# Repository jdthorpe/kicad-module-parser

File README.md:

# Convert Kicad Board and Module files to JSON

Do you love working with S-Expressions? Me either. Convert your Kicad board
and module files to JSON or YAML and use your favorite tools to work with
your Kicad board and module file data!

## CLI Usage

When installed globally (`npm i -g kicad-to-json`), npm installs the
`k2j` command line tool, which converts your kicad files to json like so:

```sh
k2j ./my_module_file.kicad_mod
# creates ./my_module_file.json in compact format

k2j ./my_board_file.kicad_pcb --yaml --format long
# creates ./my_board_file.yaml in long format
```

Use the `-h` flag for the usual help:

```txt
usage: index.js [-h] [-o OUTPUT] [-f {compact,long,bare}] [-v] [--yaml] file

Convert Kicad board and module files to JSON/YAML

positional arguments:
  file                  The Kicad pcb or module file to convert to json

optional arguments:
  -h, --help            show this help message and exit
  -o OUTPUT, --output OUTPUT
                        Output file (defaults to input file with '.json' or '.yaml' extension)
  -f {compact,long,bare}, --format {compact,long,bare}
                        Set the output format
  -v, --verbose         verbose output
  --yaml                set output to yaml
```

## Javascript / Typescript Usage

User friendly data

```ts
import { parse } from "kicad-module-parser"

// convert the module (string) to compact format
const my_module = parse.module(kicad_mod_contents_string)

// convert the board (string) to long format
const my_board = parse.board(kicad_pcb_contents_string,"long")
```

## Output Formats

### Background

The `kicad_mod` and `kicad_pcb` files are S-Expressions based which have
the general format `(name  ...contents )` where the contents are either
individual values or nested s-expressions (e.g. `( pts (xy 1 1) (xy 2 2))`).
Some s-expressions are singletons, such as the `pts` expression within a
`polygon` and others can appear multiple times, such as the individual `xy`
pairs within an array of points.

### `bare` Notation

In the `bare` notation the first token in the s-expresion appears as it's `type`
attribute, and the remaining sub-expression appear in the `value` attribute.
This format is quite literal, but generally hard to work with.  Here is a brief
example (in yaml format):

```yaml
type: kicad_pcb
value:
  - type: version
    value:
      type: number
      value: '20171130'
  - type: general
    value:
      - type: thickness
        value:
          type: number
          value: '1.6'
      - type: drawings
        value:
          type: number
          value: '605'
      - type: tracks
        value:
          type: number
          value: '2555'
      - type: zones
        value:
          type: number
          value: '0'
      - type: modules
        value:
          type: number
          value: '172'
```

### `compact` Notation

In the compact format, s-expression types and values from the bare format are
used as key-value pairs of a JSON object This works for s-expressions that are
singletons, but for expressions like `(add_net GND) (add_net +3v3)` which may
appear multiple times within the parent s-expression, the contents of the
expression are included in an array of the same name, such as :

```json
{
    "add_net":[
        {"net_name": "GND"},
        {"net_name": "+3v3"}
    ]
}
```

Here is the same example from above in compact format:

```yaml
kicad_pcb:
  version: 20171130
  general:
    thickness: 1.6
    drawings: 605
    tracks: 2555
    zones: 0
    modules: 172
    nets: 143
```

### `long` Notation

The `long` format is a hybrid between the Compact and Bare formats, and
recoginses that module and board files are special, in that nearly every file
will have *many* repeating entities (such as `gr_lines`) where preserving the
order of the entites may be useful.  Hence, the immediate children of boards and
modules (and modules nested within boards) are represent in bare format, and
everything else is represented in compact format. Here is the same example from
above in long format:

```yaml
kicad_pcb:
  - type: version
    value: 20171130
  - type: general
    value:
      thickness: 1.6
      drawings: 605
      tracks: 2555
      zones: 0
      modules: 172
      nets: 143
```

## `bare` Format Details

There are 4 primitives in the bare format which have type `"string"`, `"hex"`,
`"number"` and `"boolean"`, such as:

```json
{ "type": "string", "value": "GND" }
{ "type": "hex", "value": "1234ABCD" }
{ "type": "number", "value": "3.2" } // yes, numbers are represented as strings
{ "type": "boolean", "value": true }
```

The array type has a `type` attribute of `"array"` and a `value` contianing an
aray of primitives, such as:

```json
{ "type": "array", "value": [ { "type": "string", "value": "GND" } ] }
```

The `container` type is like the `array` type but it's `type` attribute has a
value other than `"string"`, `"hex"`, `"number"`, `"boolean"` or `"array"`, and
the value can contain any type (including other containers), or an array
containing any of the types, sucy as:

```json
{
  "type": "xy",
  "value": [
    {
      "type": "x",
      "value": {
        "type": "number",
        "value": "117.4"
      }
    },
    {
      "type": "y",
      "value": {
        "type": "number",
        "value": "28"
      }
    }
  ]
}
```

## Final notes

There are a handfule of sub-parsers and things I was not personally
interested in (such as page formatting) which result in a value like
`"page info": "unsupported"`. If you despirately need page info (or any other
unsupported features), I welcome your pull request!

If your board or module results in an error, please put it in a github repo (or
a minimal example that raises the same error), and open an issue with a link to
that github repo.

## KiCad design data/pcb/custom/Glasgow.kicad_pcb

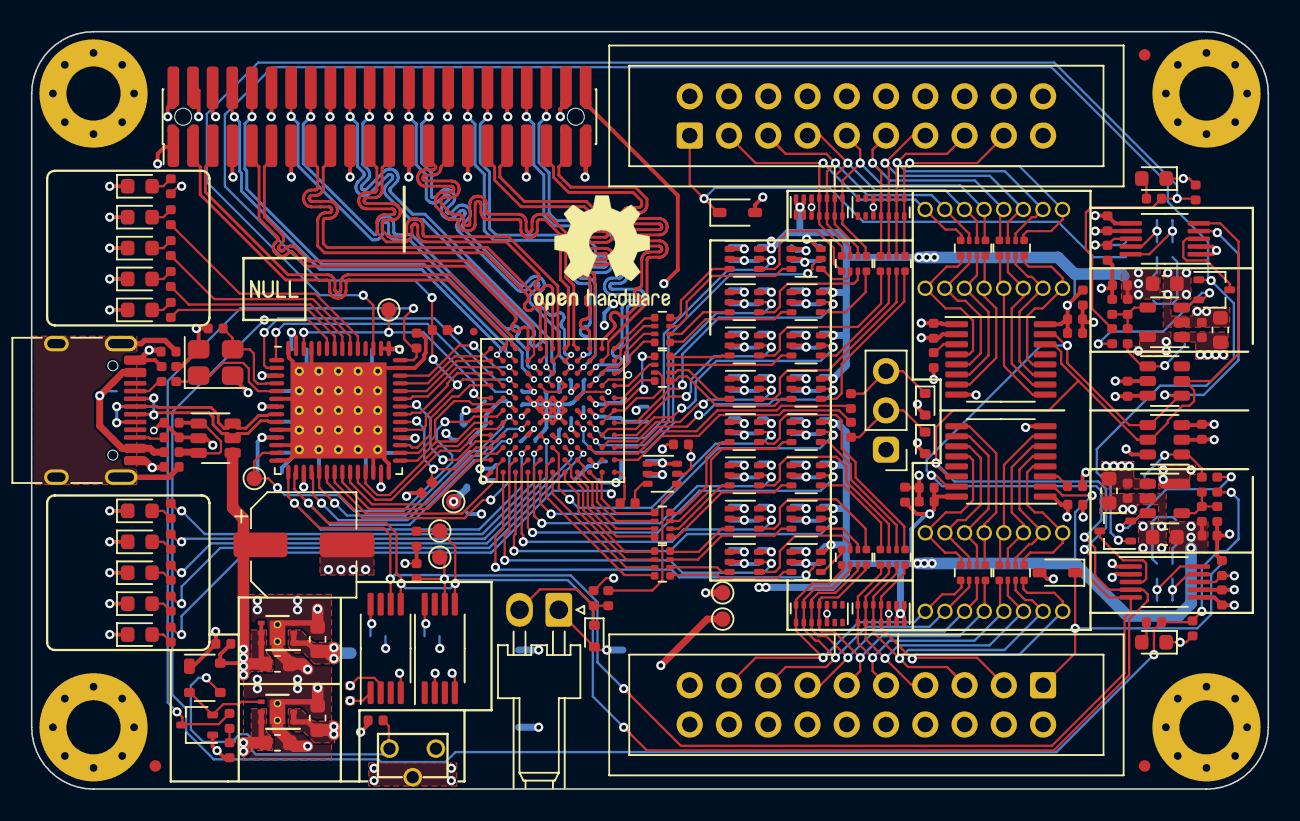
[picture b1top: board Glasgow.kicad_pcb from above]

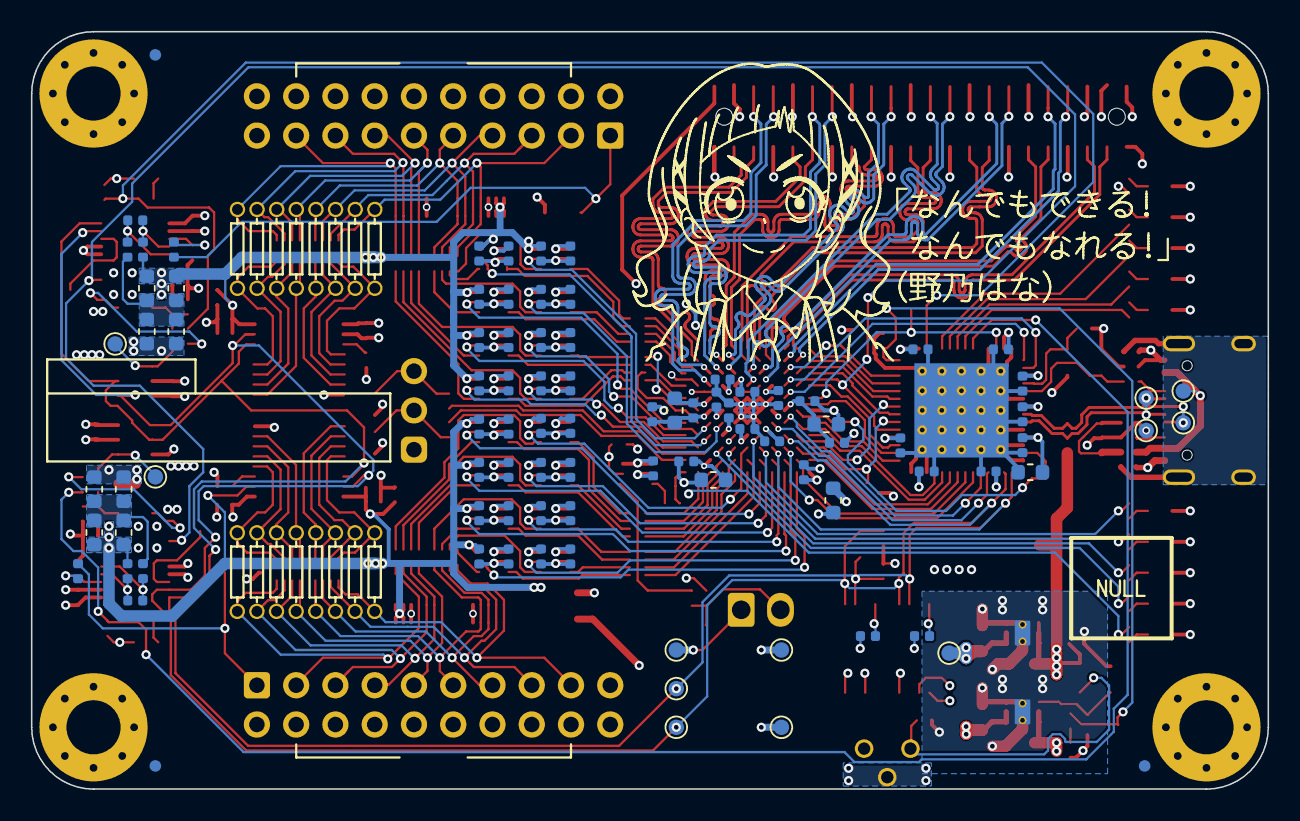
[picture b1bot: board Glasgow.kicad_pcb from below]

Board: 4 copper layers, 80.0 x 49.0 mm, 264 parts (93 on the bottom side), 226 nets.

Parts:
C1, C14, C19, C26, C27, C28, C31, C53, C76, C80, C82, C83, C86: 4u7; C_0603_1608Metric
C2, C3, C4, C5, C6, C7, C8, C9, C10, C13, C15, C16, C17, C18, C20, C21, C22, C23, C24, C25, C29, C30, C32, C33, C34, C35, C36, C37, C38, C39, C40, C41, C42, C43, C44, C45, C46, C47, C48, C49, C50, C51, C52, C54, C55, C56, C57, C58, C59, C60, C61, C62, C63, C64, C65, C66, C67, C68, C69, C70, C71, C72, C73, C74, C75, C77, C78, C79, C81, C84, C85, C88, C89: u1; C_0402_1005Metric
C11, C12: 9p; C_0402_1005Metric
C87: 150u; CP_Elec_6.3x5.9
C90, C91: DNP; C_0402_1005Metric_DNP
D1, D2, D3, D14, D15: GRN; LED_0603_1608Metric
D4: YEL; LED_0603_1608Metric
D5: RED; LED_0603_1608Metric
D6, D10: BLU; LED_0603_1608Metric
D7, D9: PNK; LED_0603_1608Metric
D8: WHT; LED_0603_1608Metric
D11, D12, D13: ESD5Z5.0T1G; D_SOD-523
D16, D17: CDSOD323-T36S; D_SOD-323
D18, D19: BAT54CW; SOT-323_SC-70
D20, D21, D22, D23: SP3012-06UTG; UDFN-14_3.5x1.35mm_P0.5mm
D24: BAT54AW; SOT-323_SC-70
FB1: 600R, 0.5A; L_0402_1005Metric
FID1, FID2, FID3, FID4, FID5, FID6: Fiducial_0.75mm_Mask1.5mm
FID8: Fiducial_0.5mm_Dia_1mm_Outer
J1: USB_C_USB2.0; USB_C_Receptacle_HRO_TYPE-C-31-M-12
J2, J3: IDC-Header_2x10_P2.54mm; IDC-Header_2x10_P2.54mm_Vertical
J4: Conn_01x02; Molex_KK-254_1x02_P2.54mm_Horizontal
J5: PinHeader_2x22_P1.27mm; PinHeader_2x22_P1.27mm_Vertical__SMD
J6, J7, J8, J9: Conn_01x08; PinSocket_1x08_P1.27mm_Vertical_DNP
J10: AUX; PinHeader_1x03_P2.54mm_Vertical
MK1, MK2, MK3, MK4: Mounting_Hole_PAD; MountingHole_3.5mm_Pad_Via_CrtYd
NONO_HANA: MECHOKKU; nono_hana_lines
R1, R2, R10, R15, R41, R42, R57, R58: 2k2; R_0402_1005Metric
R3, R4, R5, R9, R17: 100k; R_0402_1005Metric
R6, R8, R50, R51: DNP; R_0603_1608Metric_DNP
R7, R56: 0R33; R_0603_1608Metric
R11, R23: 4k7; R_0402_1005Metric
R12, R13, R14, R46, R47: 20k; R_0402_1005Metric
R16, R18, R19, R20, R22, R26, R36, R37, R44, R55: 10k; R_0402_1005Metric
R21: 6k8; R_0402_1005Metric
R24, R25, R30, R54, R59, R60: 4R7; R_0402_1005Metric
R27, R33: 49k9; R_0402_1005Metric
R28, R34: 59k; R_0402_1005Metric
R29, R35: 24k3; R_0402_1005Metric
R31, R32: 100R; R_0402_1005Metric
R38, R39, R43, R45: 47R; R_0402_1005Metric
R40: DNP; R_0402_1005Metric_DNP
R48, R49: 0R15; R_0603_1608Metric
R52, R53: 5k1; R_0402_1005Metric
RN1, RN2, RN3, RN4, RN7, RN8, RN9, RN10: 33R; R_Array_Convex_4x0402
RN5, RN6, RN11, RN12: 10k; R_Array_Convex_4x0402
SW1: RST; SW_Tactile_SPST_Angled_TC-1109DE
TP1, TP8: 5V; TestPoint_Pad_D1.0mm
TP2, TP17: 1V2; TestPoint_Pad_D1.0mm
TP3, TP7, TP9: 3V3; TestPoint_Pad_D1.0mm
TP4, TP10: SDA; TestPoint_Pad_D1.0mm
TP5, TP11: SCL; TestPoint_Pad_D1.0mm
TP6: CLKREF; TestPoint_Pad_D1.0mm
TP12: GND; TestPoint_Pad_D1.0mm
TP13: VBUS; TestPoint_Pad_D1.0mm
TP14: USBGND; TestPoint_Pad_D1.0mm
TP15: USBDP; TestPoint_Pad_D1.0mm
TP16: USBDM; TestPoint_Pad_D1.0mm
TP18, TP19: VDAC; TestPoint_Pad_D1.0mm
U1: CY7C68013A-56LTX; Cypress_QFN-56-1EP_8x8mm_P0.5mm_EP6.22x6.22mm_ThermalVias
U2: CAT24M01X; TSSOP-8_4.4x3mm_P0.65mm
U3: BL24C256A-SFRC; TSSOP-8_4.4x3mm_P0.65mm
U4, U6, U9, U10, U11, U16, U17, U18, U22, U23, U24, U25, U26, U27, U28, U29, U32: SN74LVC1T45DCKR; SOT-363_SC-70-6
U5, U19: PCA6408APW; TSSOP-16_4.4x5mm_P0.65mm
U7: APX811-40UG-7; SOT-143
U8: TLV75533PDRVR; DFN-6-1EP_2x2mm_P0.65mm_EP1x1.6mm_ThermalVias
U12, U21: INA233; VSSOP-10_3x3mm_P0.5mm
U13, U20: DAC081C081CIMK; SOT-23-6
U14, U31: TPS73101DBV; SOT-23-5
U15: TPD3S014; SOT-23-6
U30: ICE40HX8K-BG121; BGA-121_9.0x9.0mm_Layout11x11_P0.8mm_Ball0.4mm_Pad0.35mm_NS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
U36: TLV73312PQDRVR; DFN-6-1EP_2x2mm_P0.65mm_EP1x1.6mm_ThermalVias
Y1: 24M; Crystal_SMD_3225-4Pin_3.2x2.5mm

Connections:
+1V2: C14.1, C18.1, C24.1, C25.1, C27.1, C77.1, R31.2, R32.2, TP2.1, TP17.1, U30.D4, U30.D8, U30.H4, U30.H8, U36.1, U36.2
+3V3: C1.1, C2.1, C3.1, C4.1, C5.1, C6.1, C7.1, C9.1, C10.1, C15.1, C17.1, C19.1, C20.1, C21.1, C22.1, C23.1, C28.1, C30.1, C32.1, C34.1, C35.1, C36.1, C37.1, C42.1, C43.1, C47.1, C48.1, C55.1, C56.1, C60.1, C61.1, C62.1, C63.1, C68.1, C69.1, C70.1, C71.1, C81.1, C84.1, C85.1, D24.1, J5.2, R1.2, R2.2, R4.1, R12.1, R17.2, R36.2, R37.2, R40.2, R44.2, TP3.1, TP9.1, U1.3, U1.7, U1.11, U1.17, U1.27, U1.32, U1.43, U1.44, U1.55, U2.2, U2.8, U3.1, U3.8, U4.1, U5.1, U6.1, U8.1, U8.2, U9.1, U10.1, U11.1, U12.2, U12.6, U13.2, U16.1, U17.1, U18.1, U19.1, U20.2, U21.6, U22.1, U23.1, U24.1, U25.1, U26.1, U27.1, U28.1, U29.1, U30.C10, U30.D6, U30.F8, U30.H6, U30.L11, U32.1, U32.6
+5V: C16.1, C26.2, C31.1, C45.1, C59.1, C82.1, C86.2, C87.1, TP1.1, TP8.1, U7.4, U8.5, U8.6, U14.1, U15.4, U31.1, U36.4, U36.5, U36.6
/A0: U1.37, U30.K3
/A1: U1.38, U30.L2
/CC1: J1.A5, R53.2
/CC2: J1.B5, R52.2
/CLKIF: TP7.1, U1.13, U30.K6
/CLKREF: TP6.1, U1.54, U30.D5, U30.L5
/D0: U1.18, U30.H7
/D1: U1.19, U30.J7
/D2: U1.20, U30.J9
/D3: U1.21, U30.K10
/D4: U1.22, U30.L10
/D5: U1.23, U30.K9
/D6: U1.24, U30.L8
/D7: U1.25, U30.K7
/ENVA: R18.1, R47.1, R55.2, U1.45
/ENVB: R19.1, R26.2, R46.1, U1.51
/FLAGA: U1.29, U30.L7
/FLAGB: U1.30, U30.K5
/FLAGC: U1.31, U30.L4
/FLAGD: U1.40, U30.J3
/FPGA_DONE: U1.36, U30.K8
/GNDPLL0: C76.2, C78.2, U30.L6
/GNDPLL1: C79.2, C80.2, U30.C5
/IO_Banks/DA0: U4.5, U30.C7
/IO_Banks/DA1: U11.5, U30.C8
/IO_Banks/DA2: U6.5, U30.D7
/IO_Banks/DA3: U16.5, U30.A7
/IO_Banks/DA4: U9.5, U30.B8
/IO_Banks/DA5: U17.5, U30.A8
/IO_Banks/DA6: U10.5, U30.B9
/IO_Banks/DA7: U18.5, U30.A9
/IO_Banks/DB0: U22.5, U30.F9
/IO_Banks/DB1: U26.5, U30.G11
/IO_Banks/DB2: U23.5, U30.G10
/IO_Banks/DB3: U27.5, U30.H11
/IO_Banks/DB4: U24.5, U30.H10
/IO_Banks/DB5: U28.5, U30.J11
/IO_Banks/DB6: U25.5, U30.J10
/IO_Banks/DB7: U29.5, U30.K11
/IO_Banks/IO_Buffer_A/ISNS_H: R8.2, R30.1, R49.1, R51.1, R56.2
/IO_Banks/IO_Buffer_A/P0: J9.1, RN11.5, U19.4
/IO_Banks/IO_Buffer_A/P1: J9.2, RN11.6, U19.5
/IO_Banks/IO_Buffer_A/P2: J9.3, RN11.7, U19.6
/IO_Banks/IO_Buffer_A/P3: J9.4, RN11.8, U19.7
/IO_Banks/IO_Buffer_A/P4: J9.5, RN12.5, U19.9
/IO_Banks/IO_Buffer_A/P5: J9.6, RN12.6, U19.10
/IO_Banks/IO_Buffer_A/P6: J9.7, RN12.7, U19.11
/IO_Banks/IO_Buffer_A/P7: J9.8, RN12.8, U19.12
/IO_Banks/IO_Buffer_A/VDAC: R33.1, TP19.1, U20.1
/IO_Banks/IO_Buffer_A/VFB: R33.2, R34.1, R35.2, U31.4
/IO_Banks/IO_Buffer_A/VIO_EN: D19.2, R55.1, U31.3
/IO_Banks/IO_Buffer_A/VSENSE: D17.1, J2.1, R60.2
/IO_Banks/IO_Buffer_A/X0: RN7.8, U4.3
/IO_Banks/IO_Buffer_A/Y0: RN9.1, U4.4
/IO_Banks/IO_Buffer_A/Y1: RN9.2, U11.4
/IO_Banks/IO_Buffer_A/Y2: RN9.3, U6.4
/IO_Banks/IO_Buffer_A/Y3: RN9.4, U16.4
/IO_Banks/IO_Buffer_A/Y4: RN10.1, U9.4
/IO_Banks/IO_Buffer_A/Y5: RN10.2, U17.4
/IO_Banks/IO_Buffer_A/Y6: RN10.3, U10.4
/IO_Banks/IO_Buffer_A/Y7: RN10.4, U18.4
/IO_Banks/IO_Buffer_A/Z0: D22.4, D22.11, J2.3, J8.1, RN9.8, RN11.4
/IO_Banks/IO_Buffer_A/Z1: D22.3, D22.12, J2.5, J8.2, RN9.7, RN11.3
/IO_Banks/IO_Buffer_A/Z2: D22.2, D22.13, J2.7, J8.3, RN9.6, RN11.2
/IO_Banks/IO_Buffer_A/Z3: D22.1, D22.14, J2.9, J8.4, RN9.5, RN11.1
/IO_Banks/IO_Buffer_A/Z4: D23.4, D23.11, J2.11, J8.5, RN10.8, RN12.4
/IO_Banks/IO_Buffer_A/Z5: D23.3, D23.12, J2.13, J8.6, RN10.7, RN12.3
/IO_Banks/IO_Buffer_A/Z6: D23.2, D23.13, J2.15, J8.7, RN10.6, RN12.2
/IO_Banks/IO_Buffer_A/Z7: D23.1, D23.14, J2.17, J8.8, RN10.5, RN12.1
/IO_Banks/IO_Buffer_B/ISNS_H: R6.2, R7.2, R24.1, R48.1, R50.1
/IO_Banks/IO_Buffer_B/P0: J7.1, RN5.5, U5.4
/IO_Banks/IO_Buffer_B/P1: J7.2, RN5.6, U5.5
/IO_Banks/IO_Buffer_B/P2: J7.3, RN5.7, U5.6
/IO_Banks/IO_Buffer_B/P3: J7.4, RN5.8, U5.7
/IO_Banks/IO_Buffer_B/P4: J7.5, RN6.5, U5.9
/IO_Banks/IO_Buffer_B/P5: J7.6, RN6.6, U5.10
/IO_Banks/IO_Buffer_B/P6: J7.7, RN6.7, U5.11
/IO_Banks/IO_Buffer_B/P7: J7.8, RN6.8, U5.12
/IO_Banks/IO_Buffer_B/VDAC: R27.1, TP18.1, U13.1
/IO_Banks/IO_Buffer_B/VFB: R27.2, R28.1, R29.2, U14.4
/IO_Banks/IO_Buffer_B/VIO_EN: D18.2, R26.1, U14.3
/IO_Banks/IO_Buffer_B/VSENSE: D16.1, J3.1, R59.2
/IO_Banks/IO_Buffer_B/X0: RN1.8, U22.3
/IO_Banks/IO_Buffer_B/Y0: RN3.1, U22.4
/IO_Banks/IO_Buffer_B/Y1: RN3.2, U26.4
/IO_Banks/IO_Buffer_B/Y2: RN3.3, U23.4
/IO_Banks/IO_Buffer_B/Y3: RN3.4, U27.4
/IO_Banks/IO_Buffer_B/Y4: RN4.1, U24.4
/IO_Banks/IO_Buffer_B/Y5: RN4.2, U28.4
/IO_Banks/IO_Buffer_B/Y6: RN4.3, U25.4
/IO_Banks/IO_Buffer_B/Y7: RN4.4, U29.4
/IO_Banks/IO_Buffer_B/Z0: D20.4, D20.11, J3.3, J6.1, RN3.8, RN5.4
/IO_Banks/IO_Buffer_B/Z1: D20.3, D20.12, J3.5, J6.2, RN3.7, RN5.3
/IO_Banks/IO_Buffer_B/Z2: D20.2, D20.13, J3.7, J6.3, RN3.6, RN5.2
/IO_Banks/IO_Buffer_B/Z3: D20.1, D20.14, J3.9, J6.4, RN3.5, RN5.1
/IO_Banks/IO_Buffer_B/Z4: D21.4, D21.11, J3.11, J6.5, RN4.8, RN6.4
/IO_Banks/IO_Buffer_B/Z5: D21.3, D21.12, J3.13, J6.6, RN4.7, RN6.3
/IO_Banks/IO_Buffer_B/Z6: D21.2, D21.13, J3.15, J6.7, RN4.6, RN6.2
/IO_Banks/IO_Buffer_B/Z7: D21.1, D21.14, J3.17, J6.8, RN4.5, RN6.1
/IO_Banks/QA0: RN7.1, U30.A1
/IO_Banks/QA1: RN7.2, U30.A2
/IO_Banks/QA2: RN7.3, U30.B3
/IO_Banks/QA3: RN7.4, U30.A3
/IO_Banks/QA4: RN8.1, U30.B5, U30.B6
/IO_Banks/QA5: RN8.2, U30.A4
/IO_Banks/QA6: RN8.3, U30.A6, U30.B7
/IO_Banks/QA7: RN8.4, U30.A5
/IO_Banks/QB0: RN1.1, U30.B11
/IO_Banks/QB1: RN1.2, U30.C11
/IO_Banks/QB2: RN1.3, U30.D10
/IO_Banks/QB3: RN1.4, U30.D11
/IO_Banks/QB4: RN2.1, U30.E10
/IO_Banks/QB5: RN2.2, U30.E11
/IO_Banks/QB6: RN2.3, U30.F11
/IO_Banks/QB7: RN2.4, U30.F10
/IO_Banks/U1: R11.1, U30.G9
/IO_Banks/U2: R20.1, U30.G8
/IO_Banks/U3: R21.1, U30.E9
/IO_Banks/U4: R22.1, U30.D9
/IO_Banks/U5: R23.1, U30.E8
/IO_Banks/VIOA: C38.1, C39.1, C40.1, C41.1, C49.1, C50.1, C51.1, C52.1, C54.1, C57.1, C83.1, D22.6, D22.7, D22.8, D22.9, J2.2, R34.2, R42.2, R49.2, R51.2, R54.1, R58.2, U4.6, U6.6, U9.6, U10.6, U11.6, U16.6, U17.6, U18.6, U19.16
/IO_Banks/VIOB: C29.1, C46.1, C53.1, C64.1, C65.1, C66.1, C67.1, C72.1, C73.1, C74.1, C75.1, D20.6, D20.7, D20.8, D20.9, J3.2, R25.1, R28.2, R41.2, R48.2, R50.2, R57.2, U5.2, U5.16, U22.6, U23.6, U24.6, U25.6, U26.6, U27.6, U28.6, U29.6
/IO_Banks/VIO_AUX: C33.1, J5.44, U30.E4, U30.G4
/IO_Banks/Z0_N: J5.41, U30.B2
/IO_Banks/Z0_P: J5.39, U30.B1
/IO_Banks/Z1_N: J5.38, U30.C3
/IO_Banks/Z1_P: J5.40, U30.C4
/IO_Banks/Z2_N: J5.33, U30.C1
/IO_Banks/Z2_P: J5.35, U30.C2
/IO_Banks/Z3_N: J5.29, U30.D1
/IO_Banks/Z3_P: J5.27, U30.E1
/IO_Banks/Z4_N: J5.34, U30.D3
/IO_Banks/Z4_P: J5.32, U30.D2
/IO_Banks/Z5_N: J5.26, U30.E3
/IO_Banks/Z5_P: J5.28, U30.E2
/IO_Banks/Z6_N: J5.23, U30.F2
/IO_Banks/Z6_P: J5.21, U30.F1
/IO_Banks/Z7_N: J5.20, U30.F3
/IO_Banks/Z7_P: J5.22, U30.F4
/IO_Banks/Z8_N: J5.17, U30.G2
/IO_Banks/Z8_P: J5.15, U30.G1
/IO_Banks/Z9_N: J5.14, U30.H3
/IO_Banks/Z9_P: J5.16, U30.G3
/IO_Banks/Z10_N: J5.11, U30.H2
/IO_Banks/Z10_P: J5.9, U30.H1
/IO_Banks/Z11_N: J5.3, U30.K1
/IO_Banks/Z11_P: J5.5, U30.J1
/IO_Banks/Z12_N: J5.10, U30.J2
/IO_Banks/Z12_P: J5.8, U30.K2
/IO_Banks/~SYNC: D11.1, J4.2, R38.1, R44.1
/LED_ACT: R15.1, U1.49
/LED_CY: R13.1, U1.47
/LED_ERR: R16.1, U1.50
/LED_FPGA: R14.1, U1.48
/OE: U1.35, U30.L3
/PKTEND: U1.39, U30.L1
/RD: U1.1, U30.J5
/SCL: R2.1, TP5.1, TP11.1, U1.15, U2.6, U3.6, U5.14, U12.5, U13.5, U19.14, U20.5, U21.5, U30.H9
/SDA: R1.1, TP4.1, TP10.1, U1.16, U2.5, U3.5, U5.15, U12.4, U13.4, U19.15, U20.4, U21.4, U30.J8
/SHLD: C13.1, J1.S1, R3.1
/USB_N: J1.A7, J1.B7, TP16.1, U1.9, U15.5
/USB_P: J1.A6, J1.B6, TP15.1, U1.8, U15.6
/VCCPLL0: C76.1, C78.1, R31.1, U30.J6
/VCCPLL1: C79.1, C80.1, R32.1, U30.C6
/VUSB: C8.1, FB1.2, U15.1, U15.3
/WR: U1.2, U30.J4
/XTALIN: C12.1, U1.5, Y1.1
/XTALOUT: C11.1, U1.4, Y1.3
/xVBUS: FB1.1, J1.A4, J1.A9, J1.B4, J1.B9, TP13.1
/~ALERT: D18.1, D19.1, R17.1, U1.33, U30.K4
/~CY_RESET: C88.1, D24.3, R5.2, U1.42
/~FPGA_RESET: R9.2, U1.34, U30.L9
/~MR: C89.1, SW1.2, U7.3
GND: C1.2, C2.2, C3.2, C4.2, C5.2, C6.2, C7.2, C8.2, C9.2, C10.2, C11.2, C12.2, C13.2, C14.2, C15.2, C16.2, C17.2, C18.2, C19.2, C20.2, C21.2, C22.2, C23.2, C24.2, C25.2, C26.1, C27.2, C28.2, C29.2, C30.2, C31.2, C32.2, C33.2, C34.2, C35.2, C36.2, C37.2, C38.2, C39.2, C40.2, C41.2, C42.2, C43.2, C45.2, C46.2, C47.2, C48.2, C49.2, C50.2, C51.2, C52.2, C53.2, C54.2, C55.2, C56.2, C57.2, C59.2, C60.2, C61.2, C62.2, C63.2, C64.2, C65.2, C66.2, C67.2, C68.2, C69.2, C70.2, C71.2, C72.2, C73.2, C74.2, C75.2, C77.2, C81.2, C82.2, C83.2, C84.2, C85.2, C86.1, C87.2, C88.2, C89.2, C90.1, C91.1, D1.1, D2.1, D3.1, D4.1, D5.1, D6.1, D7.1, D8.1, D9.1, D10.1, D11.2, D12.2, D13.2, D14.1, D15.1, D16.2, D17.2, D20.5, D20.10, D21.5, D21.10, D22.5, D22.10, D23.5, D23.10, J1.A1, J1.A12, J1.B1, J1.B12, J2.4, J2.6, J2.8, J2.10, J2.12, J2.14, J2.16, J2.18, J3.4, J3.6, J3.8, J3.10, J3.12, J3.14, J3.16, J3.18, J4.1, J5.1, J5.4, J5.6, J5.7, J5.12, J5.13, J5.18, J5.19, J5.24, J5.25, J5.30, J5.31, J5.36, J5.37, J5.42, J5.43, J10.1, MK1.1, MK2.1, MK3.1, MK4.1, R3.2, R9.1, R10.2, R18.2, R19.2, R29.1, R35.1, R41.1, R42.1, R52.1, R53.1, R57.1, R58.1, SW1.1, TP12.1, TP14.1, U1.6, U1.10, U1.12, U1.14, U1.26, U1.28, U1.41, U1.53, U1.56, U1.57, U2.4, U3.4, U4.2, U5.8, U6.2, U7.1, U8.3, U8.7, U9.2, U10.2, U11.2, U12.1, U12.7, U13.3, U13.6, U14.2, U15.2, U16.2, U17.2, U18.2, U19.2, U19.8, U20.3, U21.1, U21.2, U21.7, U22.2, U23.2, U24.2, U25.2, U26.2, U27.2, U28.2, U29.2, U30.E5, U30.E6, U30.E7, U30.F5, U30.F6, U30.F7, U30.G5, U30.G6, U30.G7, U30.H5, U31.2, U32.2, U36.3, U36.7, Y1.2, Y1.4
unnamed: C44.1, R25.2, U12.9
unnamed: C44.2, R24.2, U12.10
unnamed: C58.1, R54.2, U21.9
unnamed: C58.2, R30.2, U21.10
unnamed: C90.2, R59.1, U12.8
unnamed: C91.2, R60.1, U21.8
unnamed: D1.2, R12.2
unnamed: D2.2, R13.2
unnamed: D3.2, R14.2
unnamed: D4.2, R15.2
unnamed: D5.2, R16.2
unnamed: D6.2, R11.2
unnamed: D7.2, R20.2
unnamed: D8.2, R21.2
unnamed: D9.2, R22.2
unnamed: D10.2, R23.2
unnamed: D12.1, J10.2, R39.1
unnamed: D13.1, J10.3, R43.1
unnamed: D14.2, R46.2
unnamed: D15.2, R47.2
unnamed: D18.3, U12.3
unnamed: D19.3, U21.3
unnamed: D24.2, U7.2, U8.4
unnamed: R4.2, R5.1
unnamed: R6.1, R7.1, U14.5
unnamed: R10.1, U30.B4, U32.5
unnamed: R36.1, U5.3
unnamed: R37.1, U19.3
unnamed: R38.2, U32.4
unnamed: R39.2, U30.A10
unnamed: R40.1, U3.2
unnamed: R43.2, U30.C9
unnamed: R45.1, U32.3
unnamed: R45.2, U30.A11
unnamed: R8.1, R56.1, U31.5
unnamed: RN1.5, U27.3
unnamed: RN1.6, U23.3
unnamed: RN1.7, U26.3
unnamed: RN2.5, U29.3
unnamed: RN2.6, U25.3
unnamed: RN2.7, U28.3
unnamed: RN2.8, U24.3
unnamed: RN7.5, U16.3
unnamed: RN7.6, U6.3
unnamed: RN7.7, U11.3
unnamed: RN8.5, U18.3
unnamed: RN8.6, U10.3
unnamed: RN8.7, U17.3
unnamed: RN8.8, U9.3

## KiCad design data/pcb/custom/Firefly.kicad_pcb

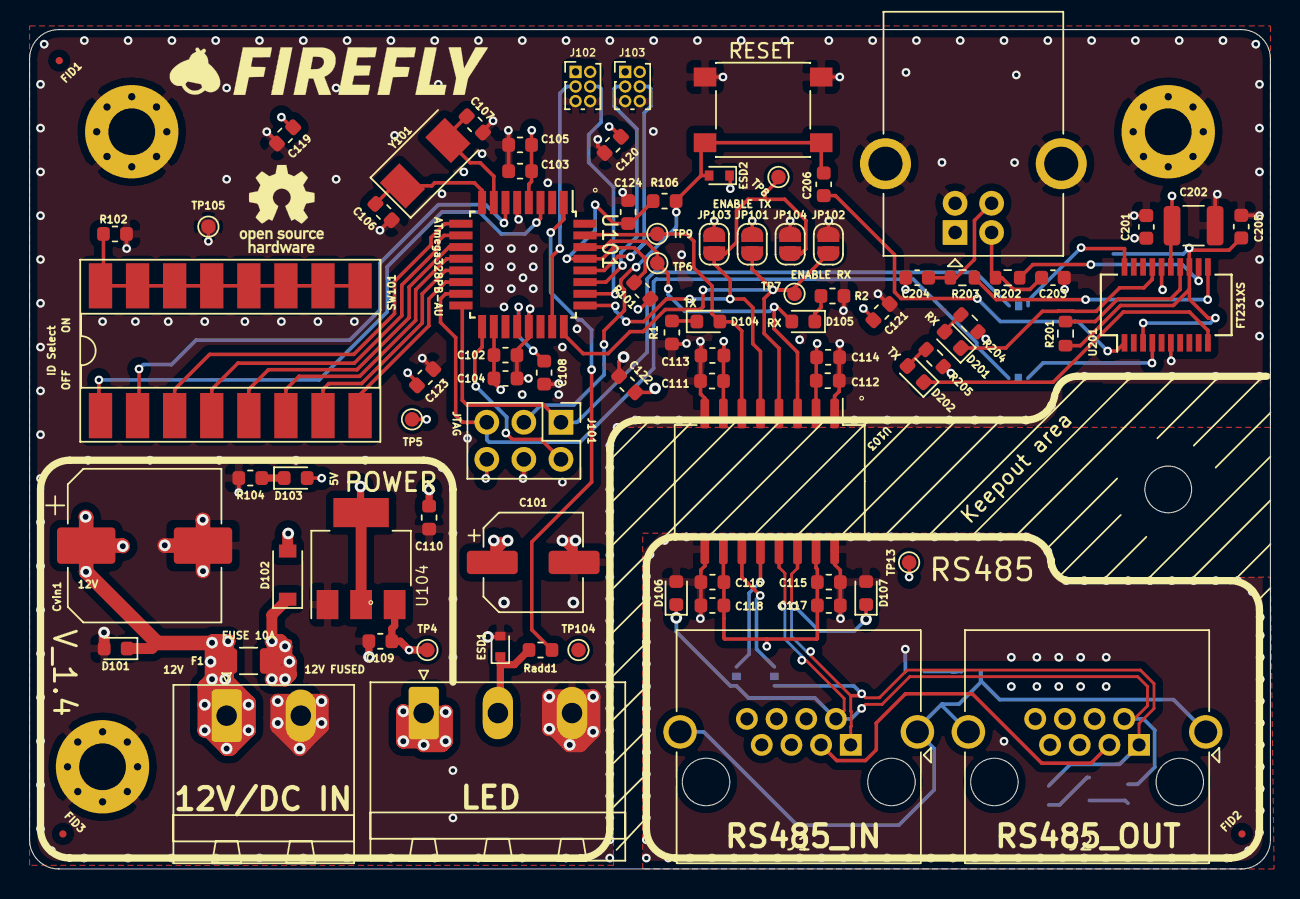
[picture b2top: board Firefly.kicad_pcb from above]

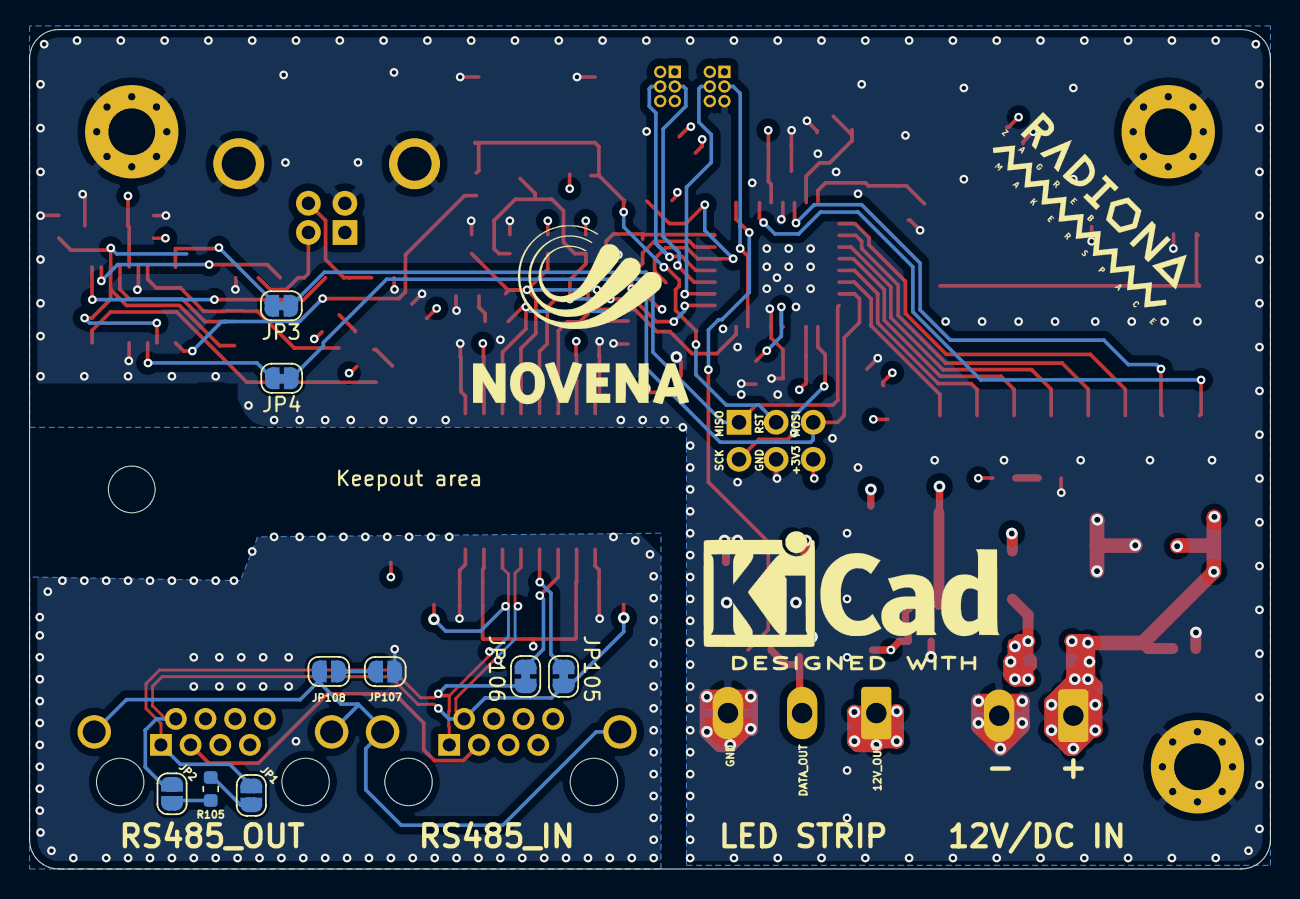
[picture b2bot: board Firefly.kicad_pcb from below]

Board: 4 copper layers, 85.0 x 57.5 mm, 99 parts (9 on the bottom side), 58 nets.

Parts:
C101: 100uF/16V; CP_Elec_6.3x5.3
C102, C103, C108, C113, C114, C117, C118, C119, C120, C121, C122, C123, C124, C206: 100n; C_0603_1608Metric
C104, C105, C111, C112, C115, C116: 10n; C_0603_1608Metric
C106, C107: 22pF; C_0603_1608Metric
C109, C110: 1uF; C_0603_1608Metric
C201, C205: 100nF; C_0603_1608Metric
C202: 4.7µF; C_1210_3225Metric
C203, C204: 47pF; C_0603_1608Metric
Cvin1: 100µF 50V 27mΩ; CP_Elec_10x10
D101, D106, D107: 82306120029; D_0603_1608Metric
D102: D_Schottky_Small; D_SOD-123
D103: LED_3V; LED_0603_1608Metric
D104, D105: LED_5V; LED_0603_1608Metric
D201: RX; LED_0603_1608Metric
D202: TX; LED_0603_1608Metric
ESD1, ESD2: PESD5V0X1UAB; D_SOD-523
F1: Fuse DNP; Fuse_1206_3216Metric_Pad1.42x1.75mm_HandSolder
FID1: FID_ATM; Fiducial_0.5mm_Mask1mm
FID2: FID_GUL; Fiducial_0.5mm_Mask1mm
FID3: FID_TLV; Fiducial_0.5mm_Mask1mm
H1, H2, H4: MountingHole; MountingHole_3.2mm_M3_Pad_Via
H3: MountingHole; MountingHole_3.2mm_M3
J1, J2: RJ45_Shielded; RJ45_Amphenol_RJHSE5380
J3: USB_B; USB_B_OST_USB-B1HSxx_Horizontal
J101: Conn_02x03_Counter_Clockwise; PinHeader_2x03_P2.54mm_Vertical
J102: Analog_1_2; PinHeader_2x03_P1.00mm_Vertical
J103: Analog_3_4; PinHeader_2x03_P1.00mm_Vertical
JP1: ET1; SolderJumper-2_P1.3mm_Open_RoundedPad1.0x1.5mm
JP2: ET2; SolderJumper-2_P1.3mm_Open_RoundedPad1.0x1.5mm
JP3: JP_FTDI_TX; SolderJumper-2_P1.3mm_Bridged_RoundedPad1.0x1.5mm
JP4: JP_FTDI_RX; SolderJumper-2_P1.3mm_Bridged_RoundedPad1.0x1.5mm
JP101: Receiver_Disable1; SolderJumper-2_P1.3mm_Open_RoundedPad1.0x1.5mm
JP102: Receiver_Enable1; SolderJumper-2_P1.3mm_Open_RoundedPad1.0x1.5mm
JP103: Driver_Enable1; SolderJumper-2_P1.3mm_Open_RoundedPad1.0x1.5mm
JP104: Driver_Disable1; SolderJumper-2_P1.3mm_Open_RoundedPad1.0x1.5mm
JP105, JP106: SolderJumper_2_Open; SolderJumper-2_P1.3mm_Bridged_RoundedPad1.0x1.5mm
JP107, JP108: SolderJumper_2_Open; SolderJumper-2_P1.3mm_Open_RoundedPad1.0x1.5mm
Jadd1: MSTBA3; PhoenixContact_MSTBA_2,5_3-G-5,08_1x03_P5.08mm_Horizontal
Jc1: MSTBA2; PhoenixContact_MSTBA_2,5_2-G-5,08_1x02_P5.08mm_Horizontal
R1, R2, R104, R106: 300; R_0603_1608Metric
R101: 4K7; R_0603_1608Metric
R102: 1K; R_0603_1608Metric
R105: 120R; R_0603_1608Metric
R201: 100K; R_0603_1608Metric
R202, R203: 27R; R_0603_1608Metric
R204, R205: 270R; R_0603_1608Metric
Radd1: 1k; R_0603_1608Metric
SW101: SW_DIP_x08; DIP-16_W8.89mm_SMDSocket_LongPads
SW102: RESET; SW_SPST_PTS645
TP4: TP_Vin; TestPoint_Pad_D1.0mm
TP5: TP_3V3; TestPoint_Pad_D1.0mm
TP6: DMX_RX; TestPoint_Pad_D1.0mm
TP7: DMX_RE; TestPoint_Pad_D1.0mm
TP8: DMX_DE; TestPoint_Pad_D1.0mm
TP9: DMX_TX; TestPoint_Pad_D1.0mm
TP13: DMX_3V3; TestPoint_Pad_D1.0mm
TP104: TP_A; TestPoint_Pad_D1.0mm
TP105: TP_GND1; TestPoint_Pad_D1.0mm
U101: ATmega328PB-AU; TQFP-32_7x7mm_P0.8mm
U103: ADM2687E; SOIC-16W_7.5x12.8mm_P1.27mm
U104: AMS1117; SOT-223-3_TabPin2
U201: FT231XS; SSOP-20_3.9x8.7mm_P0.635mm
Y101: 16MHz; Crystal_SMD_0603-2Pin_6.0x3.5mm

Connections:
+3V3: C101.1, C102.1, C103.1, C104.1, C105.1, C110.1, C111.1, C112.2, C113.2, C114.1, C119.1, C120.1, C121.1, C122.1, C123.1, C201.1, C202.1, D102.2, D103.2, ESD2.1, J3.1, J101.6, J102.1, J102.2, J103.1, J103.2, JP101.1, JP103.1, R101.2, R204.1, R205.1, TP5.1, U101.4, U101.18, U103.2, U103.7, U104.2, U201.15
/A0: J102.3, U101.23
/A3: J102.4, U101.26
/A4: J103.3, U101.27
/A5: J103.4, U101.28
/Addressable: Radd1.2, U101.1
/DMX_Enable_Receive: JP101.2, JP102.1, TP7.1, U101.24, U103.4
/DMX_Enable_Send: JP103.2, JP104.1, TP8.1, U101.25, U103.5
/DMX_Receive: D105.2, TP6.1, U101.30, U103.3
/DMX_Send: D104.2, TP9.1, U101.31, U103.6
/MISO: J101.1, JP3.1, U101.16
/MOSI: J101.5, JP4.1, U101.15
/RS485_transciever/DMX+: D107.1, J1.1, J2.1, JP1.1, JP106.2, U103.14
/RS485_transciever/DMX-: D106.1, J1.2, J2.2, JP2.2, JP105.2, U103.13
/RS485_transciever/DMXTransmitterY: JP106.1, U103.11
/RS485_transciever/DMXTransmitterZ: JP105.1, U103.12
/RS485_transciever/DMXchassignd: J1.SH, J2.SH, JP108.2
/RS485_transciever/DMXgnd: JP107.2, JP108.1
/RS485_transciever/DXMgnd: J1.3, J2.3
/RST: C206.2, ESD2.2, J101.3, R106.2, SW102.2
/SCK: J101.2, U101.17
/SW_1: SW101.1, U101.3
/SW_2: SW101.2, U101.6
/SW_3: SW101.3, U101.9
/SW_4: SW101.4, U101.10
/SW_5: SW101.5, U101.11
/SW_6: SW101.6, U101.12
/SW_7: SW101.7, U101.13
/SW_8: SW101.8, U101.14
/USB-serial/FTDI_RXD: JP4.2, U201.4
/USB-serial/FTDI_TXD: JP3.2, U201.20
/Vin: Cvin1.1, D101.1, F1.2, Jc1.1
DMX_3V: C115.1, C116.2, C117.1, C118.2, TP13.1, U103.10, U103.15
GND1: C101.2, C102.2, C103.2, C104.2, C105.2, C106.2, C107.2, C108.2, C109.2, C110.2, C111.2, C112.1, C113.1, C114.2, C119.2, C120.2, C121.2, C122.2, C123.2, C124.2, C201.2, C202.2, C203.2, C204.2, C205.1, Cvin1.2, D101.2, ESD1.2, H1.1, H2.1, H4.1, J3.4, J3.5, J101.4, J102.5, J102.6, J103.5, J103.6, JP102.2, JP104.2, Jadd1.3, Jc1.2, R1.1, R2.1, R102.1, R104.1, SW102.1, TP105.1, U101.5, U101.21, U103.1, U103.8, U104.1, U201.6, U201.16
GND2: C115.2, C116.1, C117.2, C118.1, D106.2, D107.2, JP107.1, U103.9, U103.16
unnamed: C106.1, U101.8, Y101.1
unnamed: C107.1, U101.7, Y101.2
unnamed: C108.1, U101.20
unnamed: C124.1, R101.1, R106.1, U101.29
unnamed: C203.1, J3.2, R202.2
unnamed: C204.1, J3.3, R203.2
unnamed: C205.2, R201.1, U201.3, U201.13
unnamed: C206.1, U201.1
unnamed: D103.1, R104.2
unnamed: D104.1, R1.2
unnamed: D105.1, R2.2
unnamed: D201.1, U201.17
unnamed: D201.2, R204.2
unnamed: D202.1, U201.10
unnamed: D202.2, R205.2
unnamed: ESD1.1, Jadd1.2, Radd1.1
unnamed: JP1.2, R105.1
unnamed: JP2.1, R105.2
unnamed: R102.2, SW101.9, SW101.10, SW101.11, SW101.12, SW101.13, SW101.14, SW101.15, SW101.16
unnamed: R201.2, U201.14
unnamed: R202.1, U201.12
unnamed: R203.1, U201.11
Vin_fused: C109.1, D102.1, F1.1, Jadd1.1, TP4.1, U104.3

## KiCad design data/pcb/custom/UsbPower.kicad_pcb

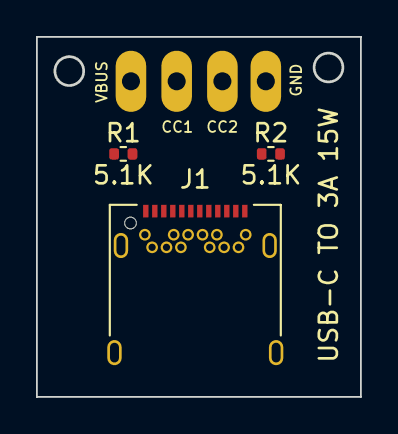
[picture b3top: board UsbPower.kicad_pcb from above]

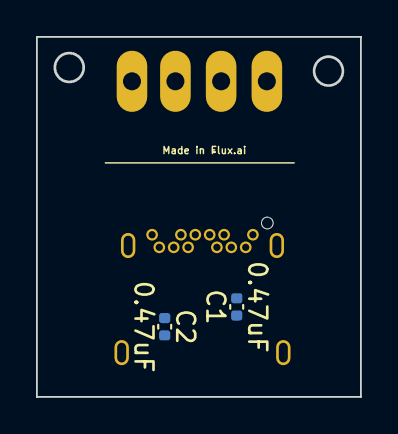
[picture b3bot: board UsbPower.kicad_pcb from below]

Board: 2 copper layers, 18.0 x 20.0 mm, 6 parts (2 on the bottom side), 7 nets, no tracks yet.

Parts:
C1, C2: 0.47uF; C_0402_1005Metric
J1: USB_C_Receptacle_USB2.0; USB_C_Receptacle_Amphenol_12401548E4-2A
J2: Conn_01x04; PinHeader_1x04_P1.27mm_Vertical_modified
R1, R2: 5.1K; R_0402_1005Metric

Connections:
GND: C1.2, C2.1, J1.A1, J1.A12, J1.B1, J1.B12, J1.S1, J2.4, R1.2, R2.2
unnamed: C1.1, J1.B8
unnamed: C2.2, J1.A4, J1.A9, J1.B4, J1.B9, J2.1
unnamed: J1.A5, J2.2, R2.1
unnamed: J1.A6, J1.B6
unnamed: J1.A7, J1.B7
unnamed: J1.B5, J2.3, R1.1

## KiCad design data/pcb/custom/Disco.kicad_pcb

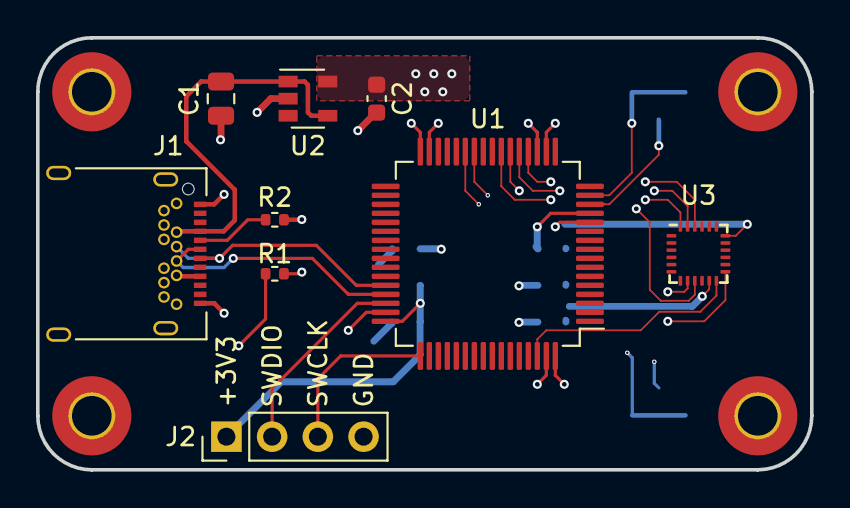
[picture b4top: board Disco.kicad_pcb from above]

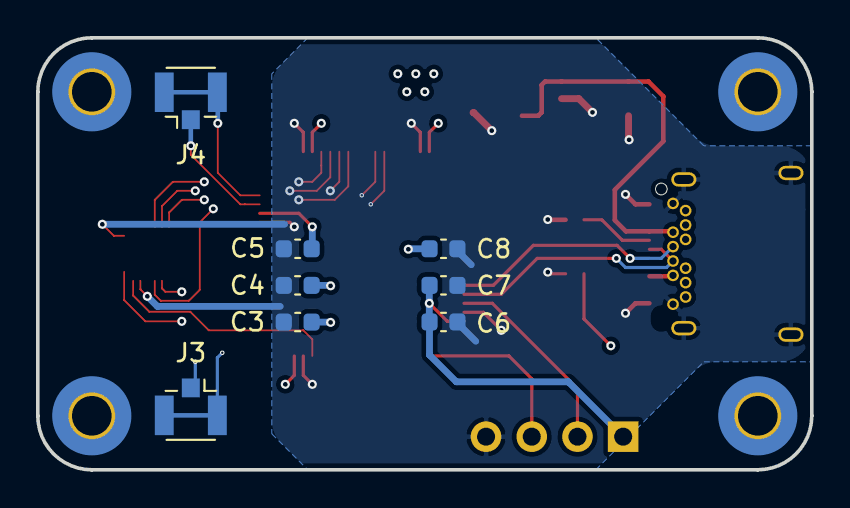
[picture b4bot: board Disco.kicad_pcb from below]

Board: 4 copper layers, 43.0 x 24.0 mm, 21 parts (8 on the bottom side), 18 nets.

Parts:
C1: 1uF/0805; C_0805_2012Metric
C2: 1uF/0603; C_0603_1608Metric
C3, C4, C5, C6, C7, C8: 0.1uF/0603; C_0603_1608Metric
H1, H2, H3, H4: MountingHole_2.2mm_M2_Pad_TopBottom
J1: USB_C_Receptacle_USB2.0; USB_C_Receptacle_Amphenol_12401548E4-2A
J2: Conn_01x04; PinHeader_1x04_P2.54mm_Vertical
J3, J4: U.FL; U.FL_Hirose_U.FL-R-SMT-1_Vertical
R1, R2: 5.1k/0402; R_0402_1005Metric
U1: STM32F103R8Tx; LQFP-64_10x10mm_P0.5mm
U2: MCP1804T-1802I/OT; SOT-23-5
U3: MPU-9250; InvenSense_QFN-24_3x3mm_P0.4mm

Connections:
+3V3: C2.1, C3.1, C4.1, C5.1, C6.1, C7.1, C8.1, J2.1, U1.13, U1.19, U1.32, U1.48, U1.64, U2.5, U3.8, U3.13
/AIN1+: J3.1, U1.26
/AIN1-: J3.2, U1.27
/AIN2+: J4.1, U1.14
/AIN2-: J4.2, U1.15
/MPU_INT: U1.62, U3.12
/SPI_CS: U1.20, U3.22
/SPI_MISO: U1.22, U3.9
/SPI_MOSI: U1.23, U3.24
/SPI_SCK: U1.21, U3.23
/SWCLK: J2.3, U1.49
/SWDIO: J2.2, U1.46
/USB+: J1.A6, J1.B6, U1.45
/USB-: J1.A7, J1.B7, U1.44
GND: C1.2, C2.2, C3.2, C4.2, C5.2, C6.2, C7.2, C8.2, J1.A1, J1.A12, J1.B1, J1.B12, J1.S1, J2.4, R1.2, R2.2, U1.12, U1.18, U1.31, U1.47, U1.63, U2.2, U3.11, U3.18
unnamed: J1.A5, R2.1
unnamed: J1.B5, R1.1
VBUS: C1.1, J1.A4, J1.A9, J1.B4, J1.B9, U2.1, U2.4

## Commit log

2020-08-09 typs
2020-08-09 minor fixes
2020-08-15 more bug fixes and a more practial wrapper function
2020-08-15 marginal improvement
2020-08-15 now exporting from index
2020-08-15 better typings?
2020-08-15 minor reformating
2020-08-15 minor updates
2020-08-15 minor bug fixw
2020-08-16 better types
2020-08-16 better types?
2020-08-17 minor bug fix
2020-08-17 bug fix
2020-08-18 bug fix?
2020-08-18 better combine
2020-08-18 width -> angle
2020-08-18 better arc
2020-08-19 better arc?
2020-08-19 better angle
2021-08-21 lots of updates
2021-08-21 cleanup
2021-08-21 better docs
2021-08-21 1.1.0
2021-08-21 typos
2021-08-21 1.1.1
2021-08-21 minor updates for clarity
2021-08-22 correcting dependency types
2021-08-22 1.1.2
2021-08-22 cli bug fix
2021-08-22 1.1.3
2021-08-22 multiple formats
2021-08-22 1.1.4
2021-08-22 typo
2021-08-22 1.1.5
2021-08-22 typing details
2021-08-22 formatting
2021-08-24 more natural order of args for parse methods
2021-08-24 1.1.6
2021-08-24 1.1.7
2021-08-24 1.1.8
2021-08-25 reverting typo
2021-12-13 add support for pcbplotparams
2021-12-14 add partial support for 'page' section
2022-05-30 JSFIX patches
2023-07-26 Update whitespace
2023-07-26 Update grammar to handle more properties
2023-07-31 Incorporate Patches from Flux
2023-08-04 Allow for wrapping layer in quotes
2024-02-14 rebuild parser
2024-03-04 Don't break on modules with `host` entry
2024-03-04 Support exponential numbers
2024-03-04 Allow for strings or symbols in `host` entry
2024-03-04 Add magic key for hosts to parse correctly
2024-03-26 Add Kicad 6 Symbol grammar
2024-03-27 Symbol tests passing
2024-03-27 Set up prettier formatting and format symbol file
2024-03-27 Clean up package.json and test build
2024-03-29 Bump version
2024-05-15 Build as proper npm ts module
    Restructure according to the guide here:
    https://pauloe-me.medium.com/typescript-npm-package-publishing-a-beginners-guide-40b95908e69c
2024-09-13 fix issues with empty lines
2024-09-17 fix color parsing bug
2024-09-17 add custom test files
2024-09-17 ignore
2024-09-17 works
2024-09-17 more tests
2024-09-17 add readme
2024-09-24 fixes
2024-09-25 more fixes
2024-09-25 footprints work
2024-09-25 refactor
2024-09-25 all test pass!!!
2024-09-25 add more test cases
